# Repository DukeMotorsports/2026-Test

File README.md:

KiCad files converted from Altium

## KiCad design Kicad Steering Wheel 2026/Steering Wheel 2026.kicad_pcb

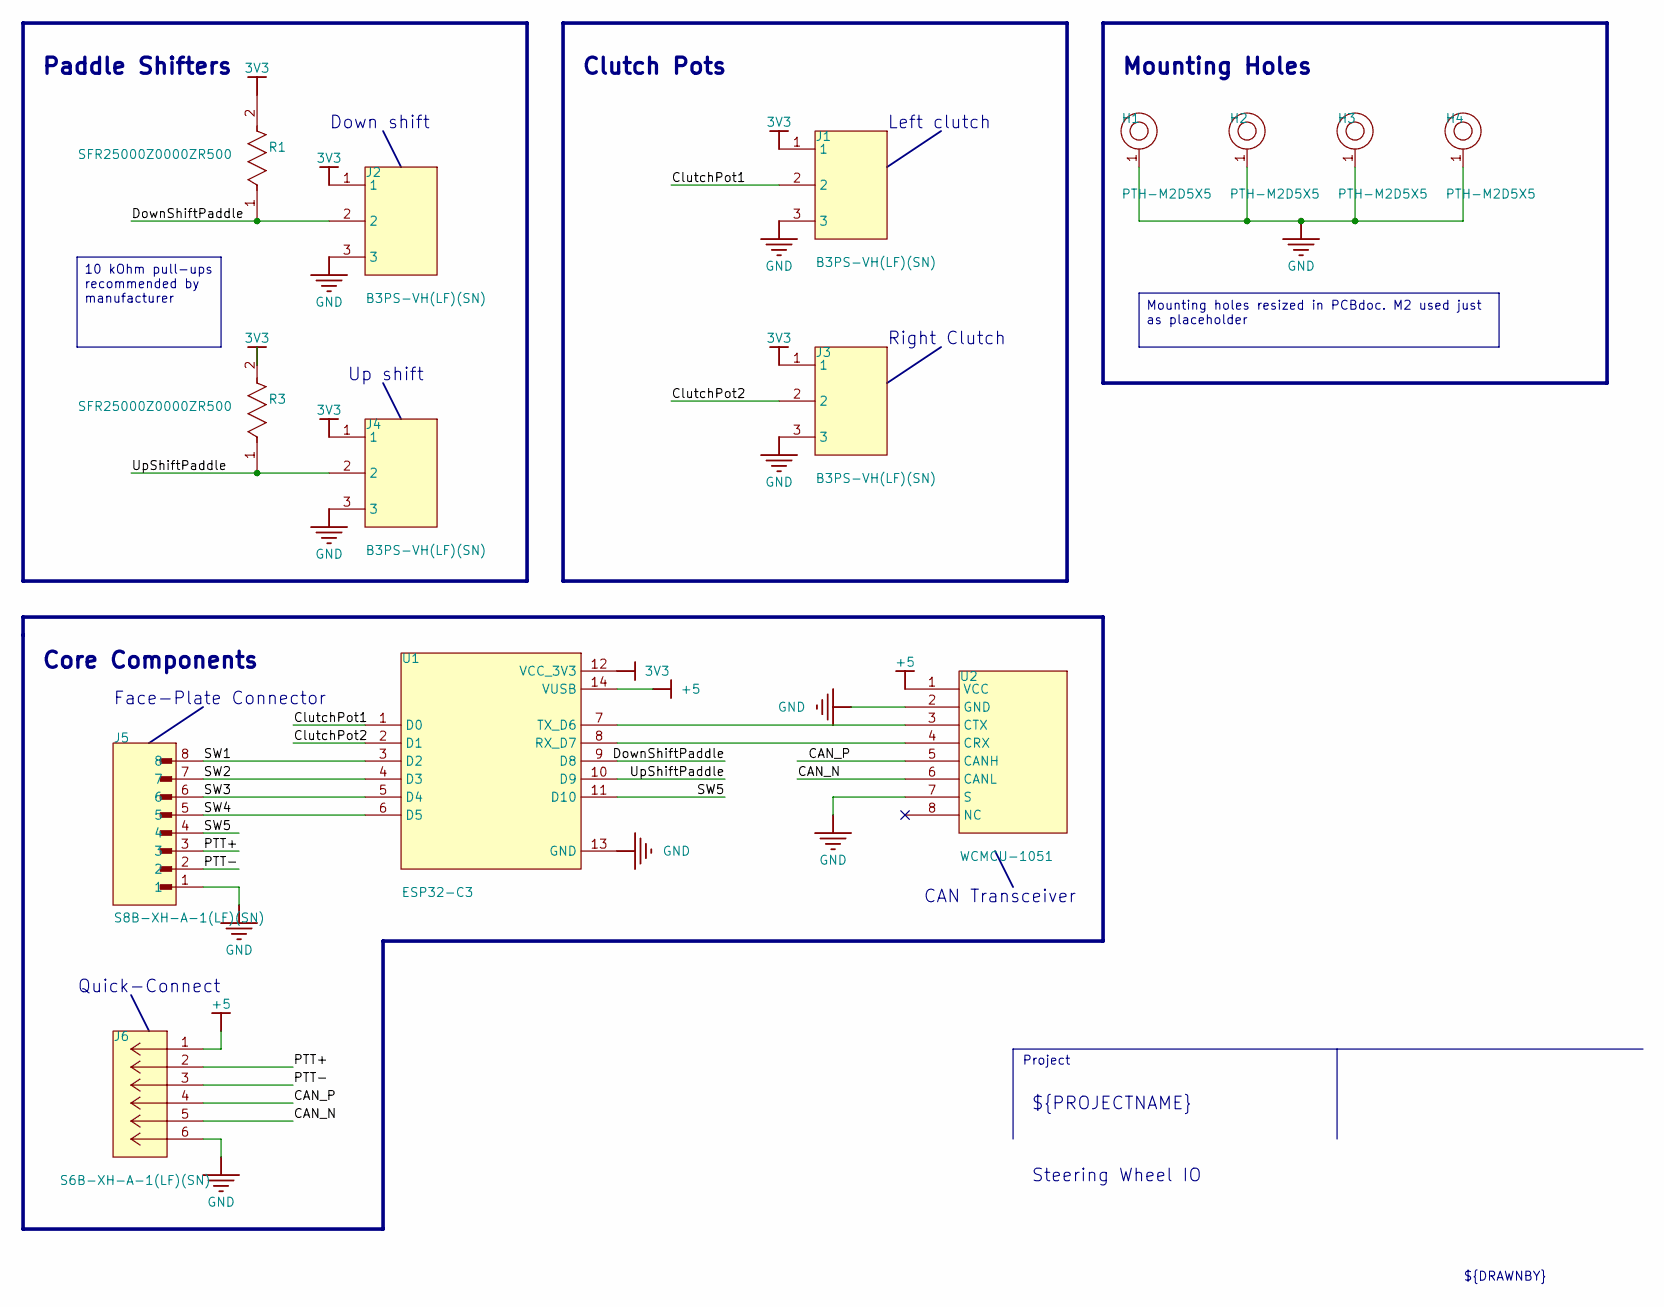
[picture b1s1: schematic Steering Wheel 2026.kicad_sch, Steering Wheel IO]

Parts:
H1, H2, H3, H4: PTH-M2D5X5
J1, J2, J3, J4: B3PS-VH(LF)(SN); JST_B3PS-VH(LF)(SN); DIGI-KEY_PART_NUMBER 455-1649-ND
J5: S8B-XH-A-1(LF)(SN); JST_S8B-XH-A-1(LF)(SN)
J6: S6B-XH-A-1(LF)(SN); CONN_S6B-XH-A_JST
R1, R3: SFR25000Z0000ZR500; FP-SFR25-MFG
U1: ESP32-C3; MODULE_113991054
U2: WCMCU-1051; WCMCU-1051-Footprint-1

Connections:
3V3: J1.1, J2.1, J3.1, J4.1, R1.2, R3.2, U1.12 (VCC_3V3)
+5: J6.1, U1.14 (VUSB), U2.1 (VCC)
CAN_N: J6.5, U2.6 (CANL)
CAN_P: J6.4, U2.5 (CANH)
ClutchPot1: J1.2, U1.1 (D0)
ClutchPot2: J3.2, U1.2 (D1)
DownShiftPaddle: J2.2, R1.1, U1.9 (D8)
GND: H1.1, H2.1, H3.1, H4.1, J1.3, J2.3, J3.3, J4.3, J5.1, J6.6, U1.13 (GND), U2.2 (GND), U2.7 (S)
NetU1_7: U1.7 (TX_D6), U2.3 (CTX)
NetU1_8: U1.8 (RX_D7), U2.4 (CRX)
PTT+: J5.3, J6.2
PTT-: J5.2, J6.3
SW1: J5.8, U1.3 (D2)
SW2: J5.7, U1.4 (D3)
SW3: J5.6, U1.5 (D4)
SW4: J5.5, U1.6 (D5)
SW5: J5.4, U1.11 (D10)
UpShiftPaddle: J4.2, R3.1, U1.10 (D9)

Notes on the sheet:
Face-Plate Connector
Paddle Shifters
Mounting Holes
Right Clutch
Quick-Connect
Left clutch
${PROJECTNAME}
${TITLE}
Down shift
Clutch Pots
Up shift
CAN Transceiver
${DRAWNBY}
Core Components
Project
Mounting holes resized in PCBdoc. M2 used just as placeholder
10 kOhm pull-ups recommended by manufacturer

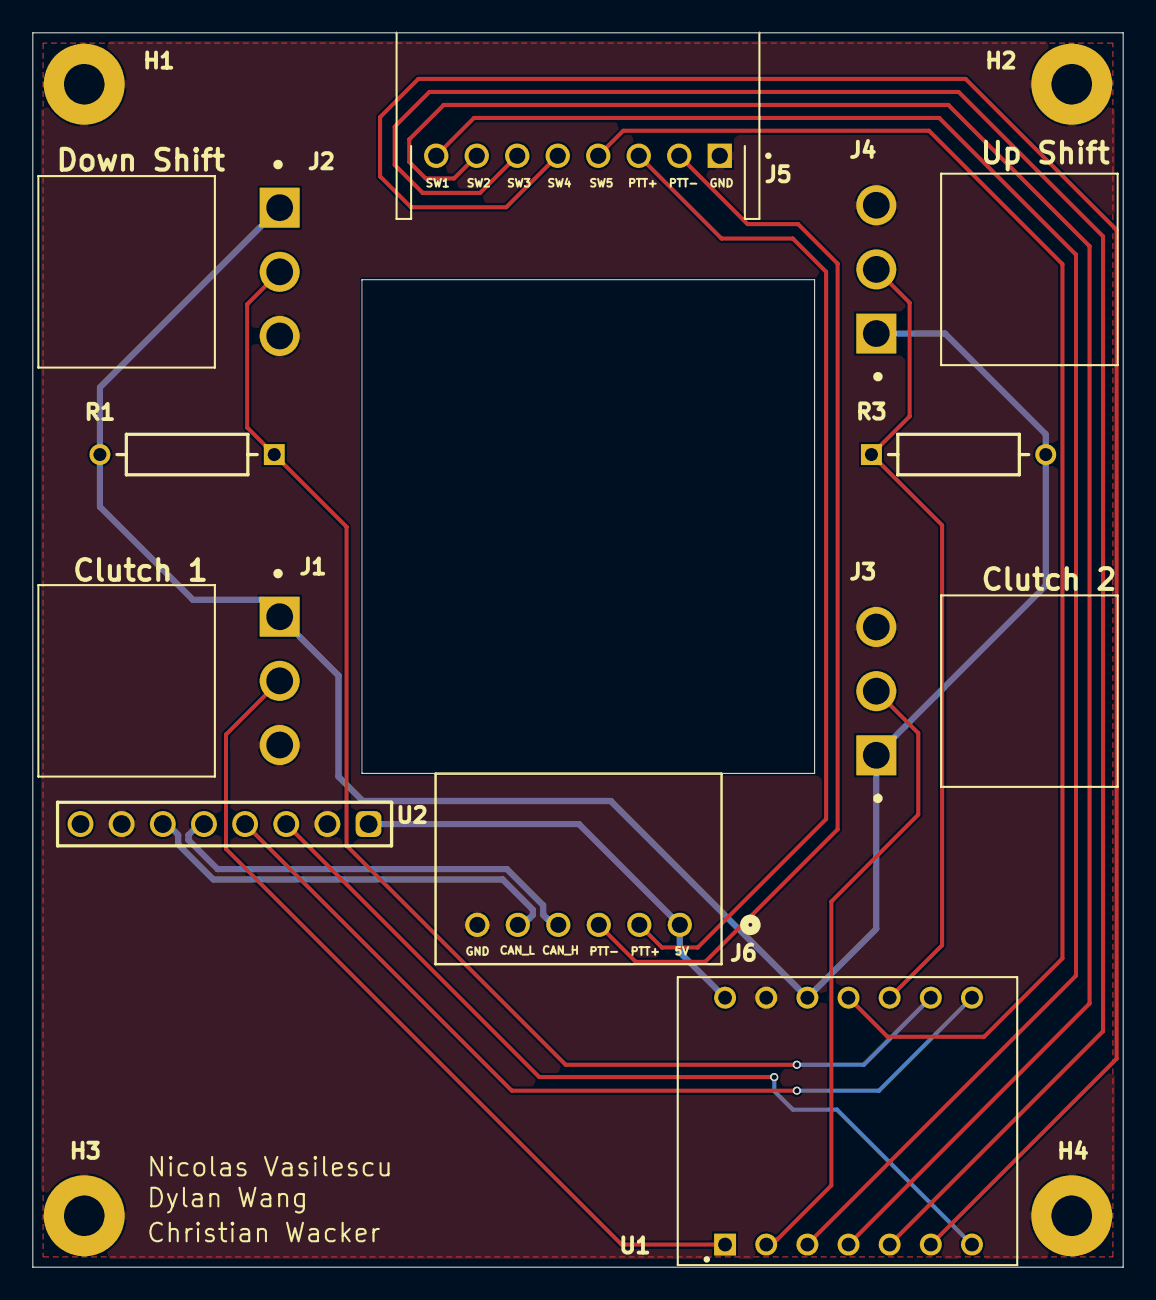
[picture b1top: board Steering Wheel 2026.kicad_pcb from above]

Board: 2 copper layers, 67.3 x 76.2 mm, 14 parts (0 on the bottom side), 18 nets.

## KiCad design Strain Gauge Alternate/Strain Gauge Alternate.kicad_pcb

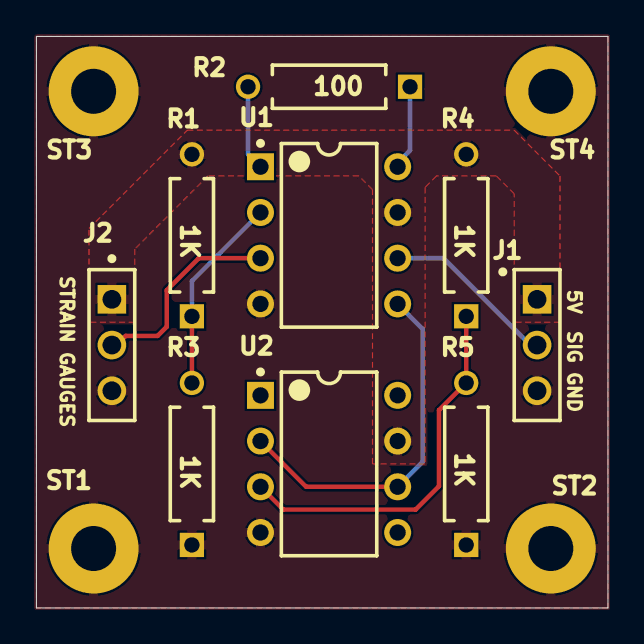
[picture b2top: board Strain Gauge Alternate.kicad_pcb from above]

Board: 2 copper layers, 31.8 x 31.8 mm, 13 parts (0 on the bottom side), 9 nets.

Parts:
J1, J2: SSW-103-01-G-S; FP-SSW-103-01-G-S-MFG
R1, R2, R3, R4, R5: MFR-25FBF52-47R5; RESA60-630X240
ST1, ST2, ST3, ST4: PTH-M2D5X5
U1: INA121PA; P0008A
U2: UA741CP; P0008A

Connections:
5V: J1.1, J2.1, R1.2, R4.2, U1.7, U2.7
GND: J1.3, J2.3, R3.1, R5.1, ST1.1, ST2.1, ST3.1, ST4.1, U1.4, U2.4
NetJ1_2: J1.2, U1.6
NetJ2_2: J2.2, U1.3
NetR1_1: R1.1, R3.2, U1.2
NetR2_1: R2.1, U1.8
NetR2_2: R2.2, U1.1
NetR4_1: R4.1, R5.2, U2.3
NetU1_5: U1.5, U2.2, U2.6
